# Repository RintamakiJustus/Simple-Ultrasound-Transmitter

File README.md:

# Simple-Ultrasound-Transmitter
Simple ultrasound transmitter utilizing piezoelectric ultrasound transducer driven by microcontroller.

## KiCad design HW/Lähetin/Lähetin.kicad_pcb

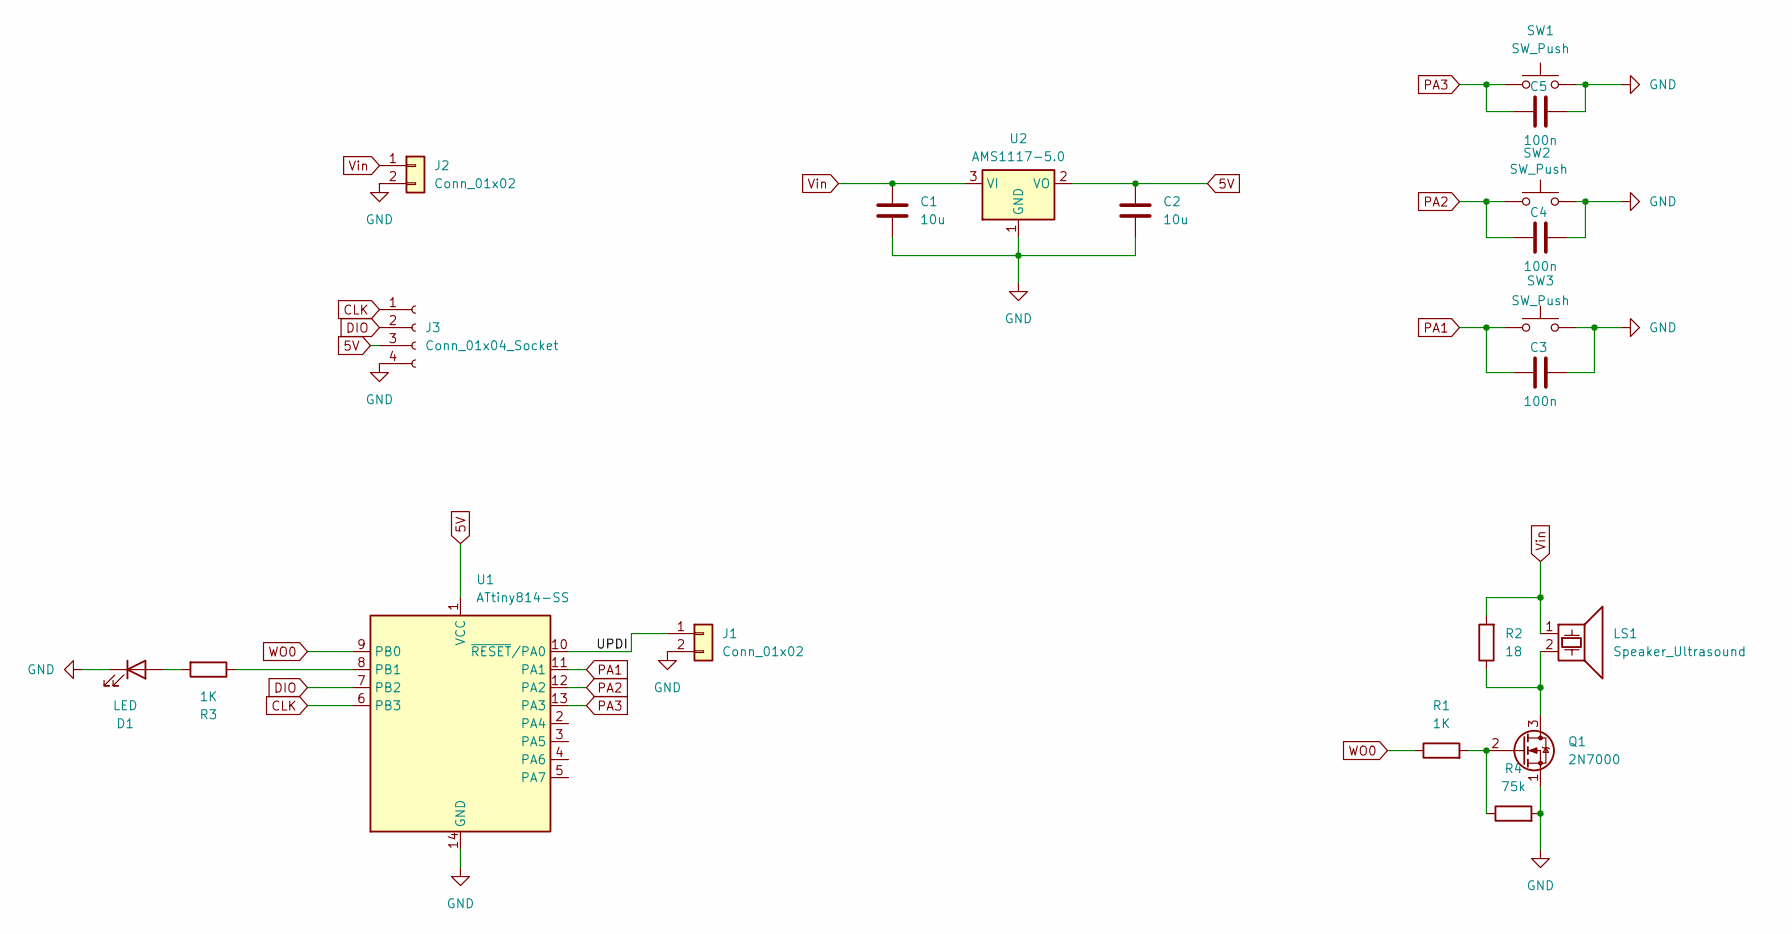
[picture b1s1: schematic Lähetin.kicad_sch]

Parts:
C1, C2: 10u; C_0603_1608Metric_Pad1.08x0.95mm_HandSolder
C3, C4, C5: 100n; C_0603_1608Metric_Pad1.08x0.95mm_HandSolder
D1: LED; C_0603_1608Metric_Pad1.08x0.95mm_HandSolder
J1, J2: Conn_01x02; JST_EH_B2B-EH-A_1x02_P2.50mm_Vertical
J3: Conn_01x04_Socket; PinHeader_1x04_P2.54mm_Vertical
LS1: Speaker_Ultrasound; Buzzer_12x9.5RM7.6
Q1: 2N7000; TO-92_Inline
R1, R3: 1K; C_1206_3216Metric_Pad1.33x1.80mm_HandSolder
R2: 18; R_Axial_Power_L20.0mm_W6.4mm_P25.40mm
R4: 75k; C_1206_3216Metric_Pad1.33x1.80mm_HandSolder
SW1, SW2, SW3: SW_Push; SW_Tactile_SPST_Angled_PTS645Vx39-2LFS
U1: ATtiny814-SS; SOIC-14_3.9x8.7mm_P1.27mm
U2: AMS1117-5.0; SOT-223-3_TabPin2

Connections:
5V: C2.1, J3.3, U1.1 (VCC), U2.2 (VO)
/UPDI: J1.1, U1.10 (~RESET/PA0)
CLK: J3.1, U1.6 (PB3)
DIO: J3.2, U1.7 (PB2)
GND: C1.2, C2.2, C3.2, C4.2, C5.2, D1.1 (K), J1.2, J2.2, J3.4, Q1.1 (S), R4.2, SW1.2, SW2.2, SW3.2, U1.14 (GND), U2.1 (GND)
unnamed: D1.2 (A), R3.2
unnamed: LS1.2, Q1.3 (D), R2.1
unnamed: Q1.2 (G), R1.2, R4.1
unnamed: R3.1, U1.8 (PB1)
PA1: C3.1, SW3.1, U1.11 (PA1)
PA2: C4.1, SW2.1, U1.12 (PA2)
PA3: C5.1, SW1.1, U1.13 (PA3)
Vin: C1.1, J2.1, LS1.1, R2.2, U2.3 (VI)
WO0: R1.1, U1.9 (PB0)

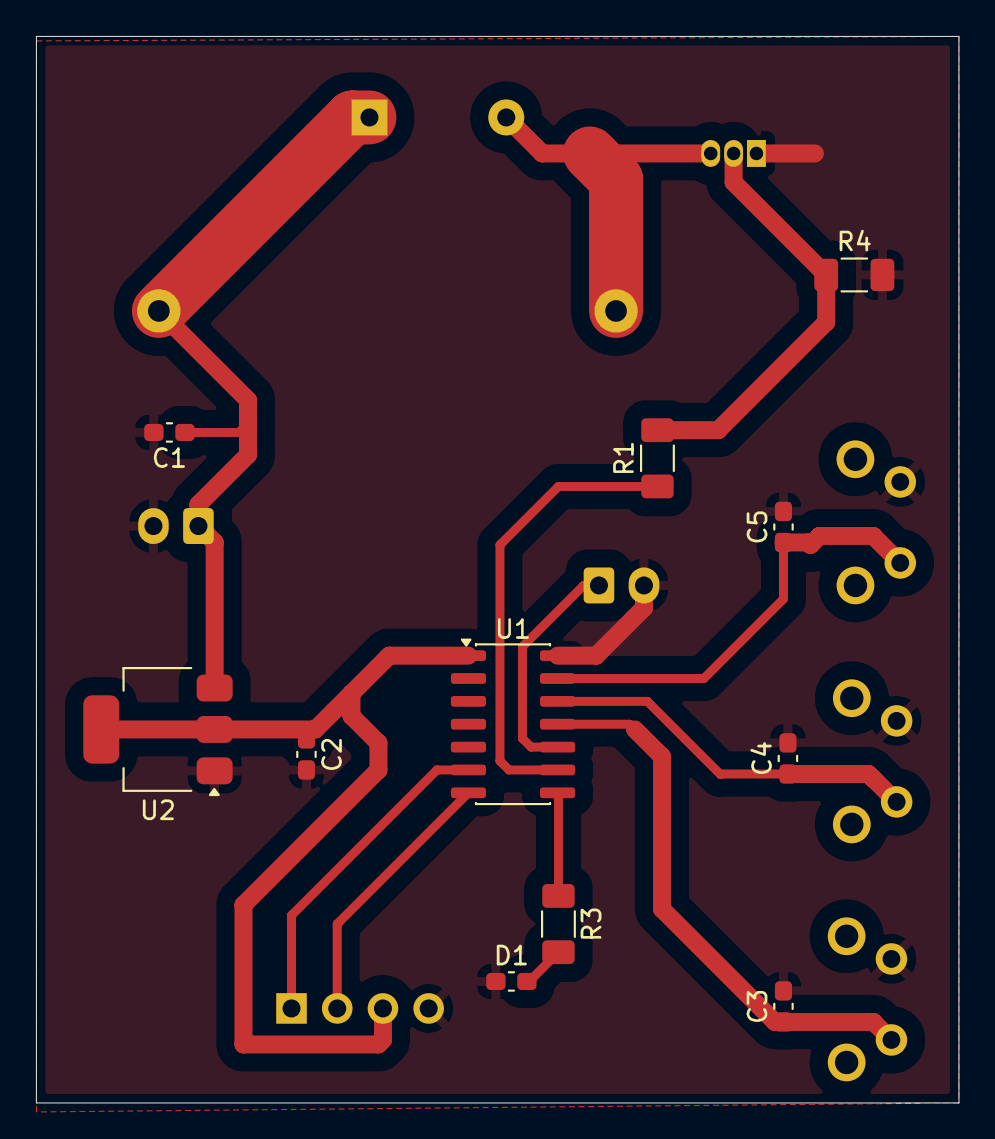
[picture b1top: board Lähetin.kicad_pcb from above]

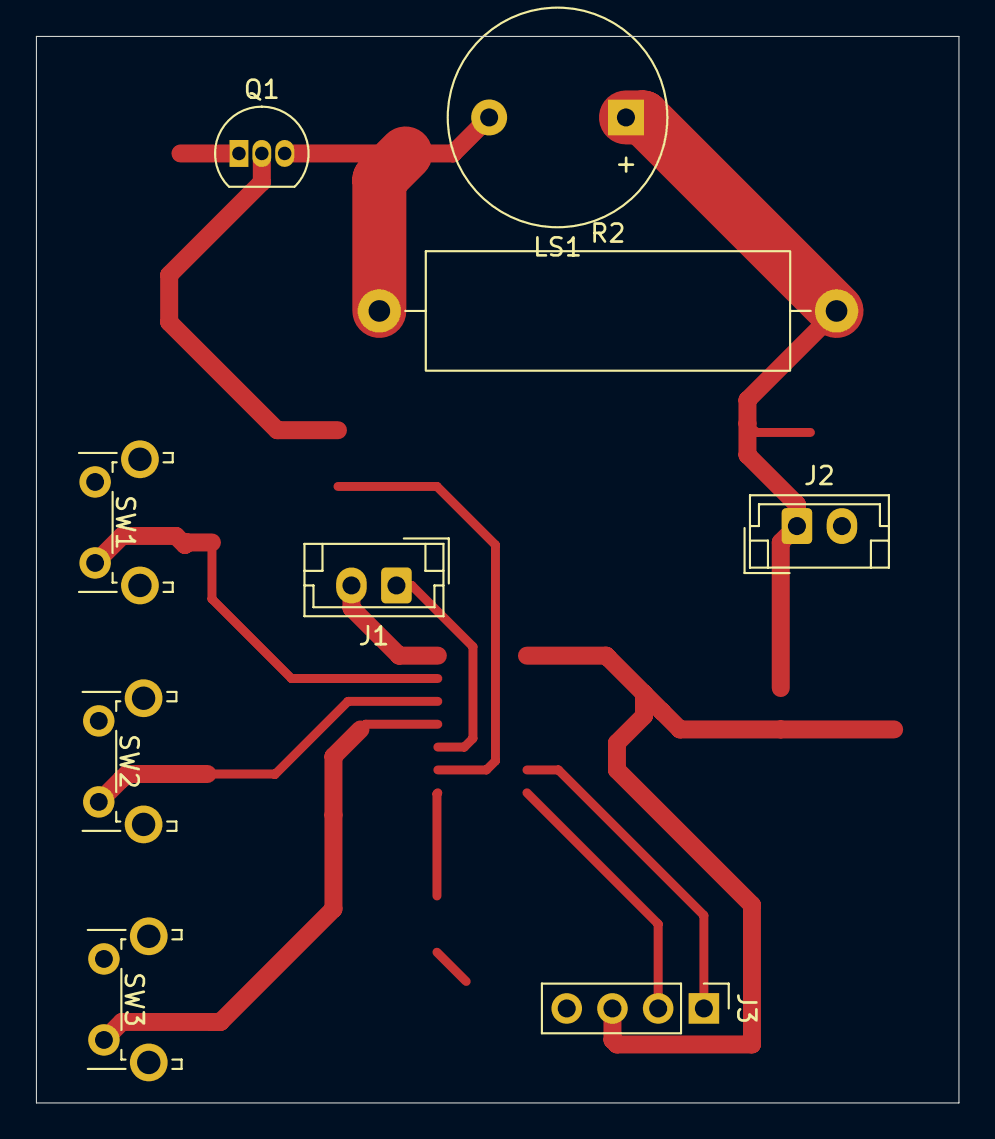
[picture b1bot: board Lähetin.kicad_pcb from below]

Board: 2 copper layers, 51.2 x 59.2 mm, 20 parts (9 on the bottom side), 14 nets.

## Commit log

2026-03-10 Added HW and SW files
2026-03-14 Fixed bugs in SW
2026-03-27 Fixed correct freqency transmission, shows frequency in kilohertz
